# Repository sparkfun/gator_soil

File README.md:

SparkFun gator:soil - micro:bit Accessory Board 
=============================

[*SparkFun gator:soil - micro:bit Accessory Board (SEN-15272)*](https://www.sparkfun.com/products/15272)

(Modify Description)
A simple breakout to aid in the measuring of moisture in soil and similar materials. 

Repository Contents
-------------------

* **/Hardware** - Eagle design files (.brd, .sch)
* **/Production** - Production panel files (.brd)

Documentation
--------------

* **[Hookup Guide](https://learn.sparkfun.com/tutorials/sparkfun-gatorsoil-hookup-guide)** - Basic hookup guide for the gator:soil.
* **[gator:soil PXT Package](https://github.com/sparkfun/pxt-gator-soil)** - PXT- package for the MakeCode gator:soil extension.

License Information
-------------------

This product is _**open source**_! 

Please review the LICENSE.md file for license information. 

If you have any questions or concerns on licensing, please visit the [SparkFun Forum](https://forum.sparkfun.com/index.php) and post a topic. For more general questions related to our gator boards, please visit this section of the forum: [SparkFun Forums: Educational Products](https://forum.sparkfun.com/viewforum.php?f=155)

Distributed as-is; no warranty is given.

- Your friends at SparkFun.

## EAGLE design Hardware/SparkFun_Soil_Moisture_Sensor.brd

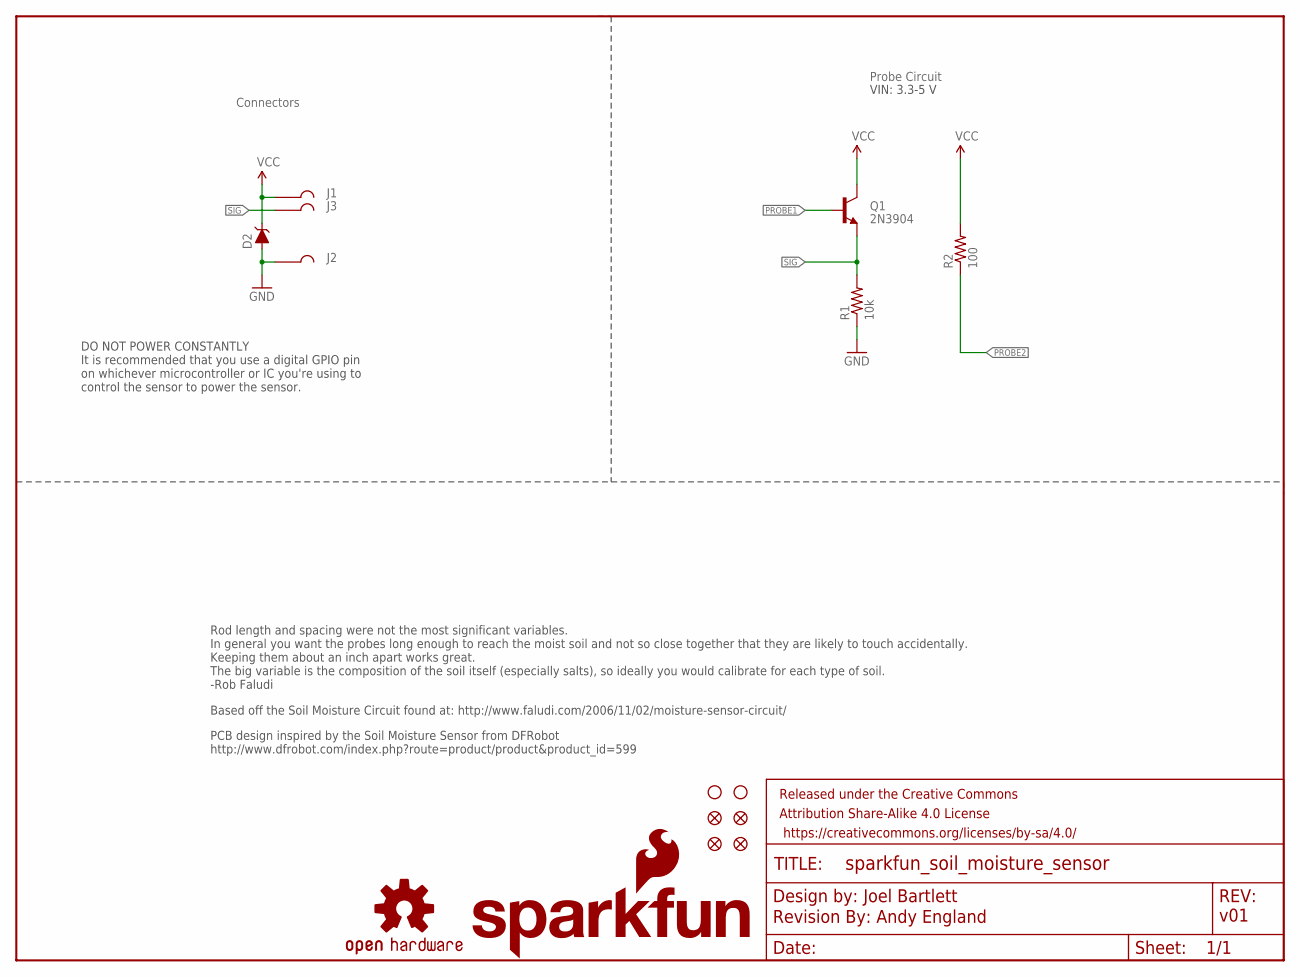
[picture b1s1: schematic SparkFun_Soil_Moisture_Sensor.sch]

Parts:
D2: 3.6V; SOD-323
FID1, FID2, FID3, FID4: FIDUCIAL1X2; FIDUCIAL-1X2
FRAME1: FRAME-LETTER; CREATIVE_COMMONS
J1, J2, J3: GATORGATOR_MINI; GATOR_MINI
LOGO1: SFE_LOGO_NAME_FLAME.1_INCH; SFE_LOGO_NAME_FLAME_.1
LOGO2: OSHW-LOGOS; OSHW-LOGO-S
LOGO3: REVISION
Q1: 2N3904; SOT23-3@1
R1: 10k; 0603
R2: 100; 0603
STANDOFF1, STANDOFF2: STAND-OFF

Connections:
GND: D2.A, J2.P$2, R1.1
PROBE1: Q1.1 (B)
PROBE2: R2.1
SIG: J3.P$2, Q1.2 (E), R1.2
VCC: D2.C, J1.P$2, Q1.3 (C), R2.2

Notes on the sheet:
Based off the Soil Moisture Circuit found at: http://www.faludi.com/2006/11/02/moisture-sensor-circuit/
Rod length and spacing were not the most significant variables. In general you want the probes long enough to reach the moist soil and not so close together that they are likely to touch accidentally. Keeping them about an inch apart works great. The big variable is the composition of the soil itse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
Connectors
Probe Circuit
DO NOT POWER CONSTANTLY It is recommended that you use a digital GPIO pin on whichever microcontroller or IC you're using to control the sensor to power the sensor.
PCB design inspired by the Soil Moisture Sensor from DFRobot http://www.dfrobot.com/index.php?route=product/product&product_id=599
Andy England
v01
VIN: 3.3-5 V

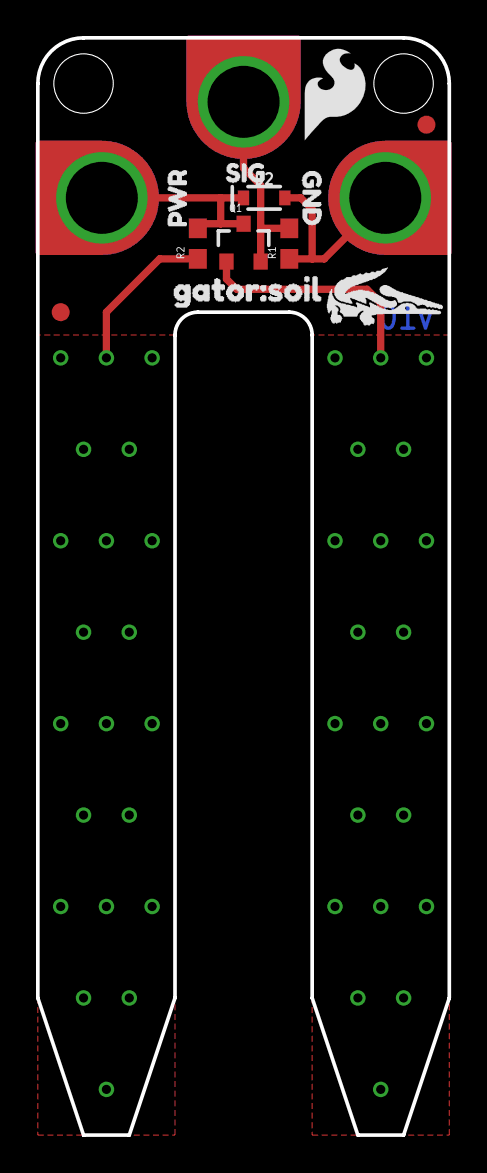
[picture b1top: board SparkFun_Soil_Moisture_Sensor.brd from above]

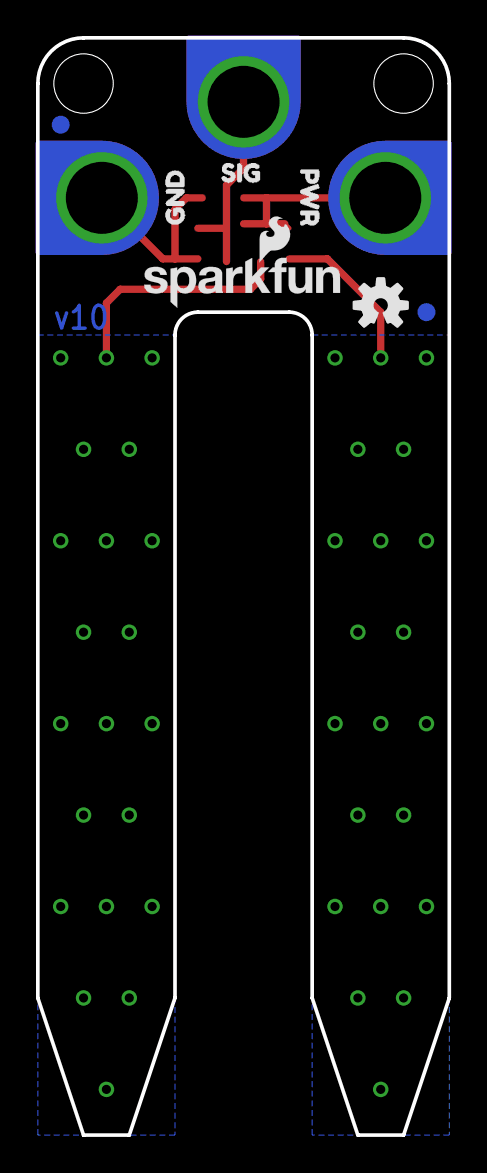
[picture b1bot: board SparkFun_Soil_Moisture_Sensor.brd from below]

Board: 2 copper layers, 22.9 x 61.0 mm, 27 parts (7 on the bottom side), 3 nets.

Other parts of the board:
U$1, U$6: PWR2
U$2, U$7: GND0
U$3, U$5: SIG1
U$4: SFE_LOGO_FLAME_.2
U$8: GATOR#SOIL1
U$10: ORDERING_INSTRUCTIONS
U$11: GATORBIT_FINAL_FOR_SILK#01#PNG

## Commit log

2019-02-25 initial commit, chanigng to gator tabs
2019-02-25 updating silk, fiducials
2019-02-28 adding protection circuitry
2019-02-28 finalizing silk and schematic before design review
2019-03-01 engineer run of checklist
2019-03-08 post qc double check, ordering protos
2019-04-02 updating 100 ohm resistor
2019-04-19 centering gator silk
2019-06-12 Update to current product information
    Will need to update forum link and description
2019-06-12 Update
    Troubleshooting link and product description
2019-06-14 cleaning repo

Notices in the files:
parts and their libraries:
SparkFun-DiscreteSemi: Licensing: Creative Commons ShareAlike 4.0 International - https://creativecommons.org/licenses/by-sa/4.0
SparkFun-Aesthetics: Released under the Creative Commons Attribution Share-Alike 4.0 License
SparkFun-Aesthetics: https://creativecommons.org/licenses/by-sa/4.0
